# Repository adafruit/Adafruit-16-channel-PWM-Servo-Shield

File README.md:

# PCB for the Adafruit 16-channel PWM/Servo shield

__Format is EagleCAD schematic and board layout__

<a href="http://www.adafruit.com/products/1411"><br/>Click here to purchase one from the Adafruit shop</a>

You want to make a cool Arduino robot, maybe a hexapod walker, or maybe just a piece of art with a lot of moving parts. Or maybe you want to drive a lot of LEDs with precise PWM output. Then you realize that the Arduino has only a few PWM outputs, and maybe those outputs are conflicting with another shield! What now? You could give up OR you could just get our handy PWM and Servo driver shield. It's just like our popular PWM/Servo Breakout but now Arduino-ready and works with any Arduino that uses shields: Uno, Leo, Mega, ADK, its all good.

When we saw this chip, we quickly realized what an excellent add-on this would be. __Using only two I2C pins, control 16 free-running PWM outputs!__ You can even stack up 62 shields to control up to 992 PWM outputs (which we would really like to see since it would be glorious and like 4 feet tall) Because I2C is a shared bus you can also connect other I2C devices and sensors to the SCL/SDA pins as long as their addresses don't conflict (this shield has address 0x40)

- There's an I2C-controlled PWM driver with a built in clock. That means that, unlike the TLC5940 family, you do not need to continuously send it signal tying up your microcontroller, its completely free running!
- It is 5V compliant, which means you can control it from a 3.3V Arduino and still safely drive up to 6V outputs (this is good for when you want to control white or blue LEDs with 3.4+ forward voltages)
- 6 address select pins so you can stack up to 62 of these on a single i2c bus. 12 out of 16 output pins can be accessed when stacked.
- Adjustable frequency PWM up to about 1.6 KHz
- 12-bit resolution for each output - for servos, that means about 4us resolution at 60Hz update rate
- Configurable push-pull or open-drain output

We wrapped up this lovely chip into a shield with a couple nice extras

- Terminal block for power input (or you can use the 0.1" breakouts on the side)
- Reverse polarity protection on the terminal block input
- Green and red power-good LEDs
- 3 pin connectors in groups of 4 so you can plug in 16 servos at once (Servo plugs are slightly wider than 0.1" so you can only stack 4 next to each other on 0.1" header
- Stackable design. You'll need to pick up stacking headers and right angle 3x4 headers in order to stack on top of this shield without the servo connections getting in the way.
- A spot to place a big capacitor on the V+ line (in case you need it)
- 220 ohm series resistors on all the output lines to protect them, and to make driving LEDs trivial
- Solder jumpers for the 6 address select pins
- A lot of extra space remaining? Let's turn it into a prototyping area. You get a 5x20 proto area for any extra wiring you'd like to add

This product comes with a fully tested and assembled shield as well as 4 pieces of 3x4 male straight header (for servo/LED plugs), a 2-pin terminal block (for power) and a stick of 0.1" header so you can plug into an Arduino. A little light soldering will be required to assemble and customize the board by attaching the desired headers but it is a 15 minute task that even a beginner can do. [If you want to use right-angle 3x4 headers, we also carry a 4 pack in the shop - note that only 3 of them can be used when stacking (12 servos total)](http://www.adafruit.com/products/816).

__Servos and Arduino not included__ - but we do sell tons of different servos in the shop so pick up a few while you're here!

## License

Adafruit invests time and resources providing this open source design, 
please support Adafruit and open-source hardware by purchasing 
products from Adafruit!

Designed by Adafruit Industries.  
Creative Commons Attribution, Share-Alike license, check license.txt for more information
All text above must be included in any redistribution

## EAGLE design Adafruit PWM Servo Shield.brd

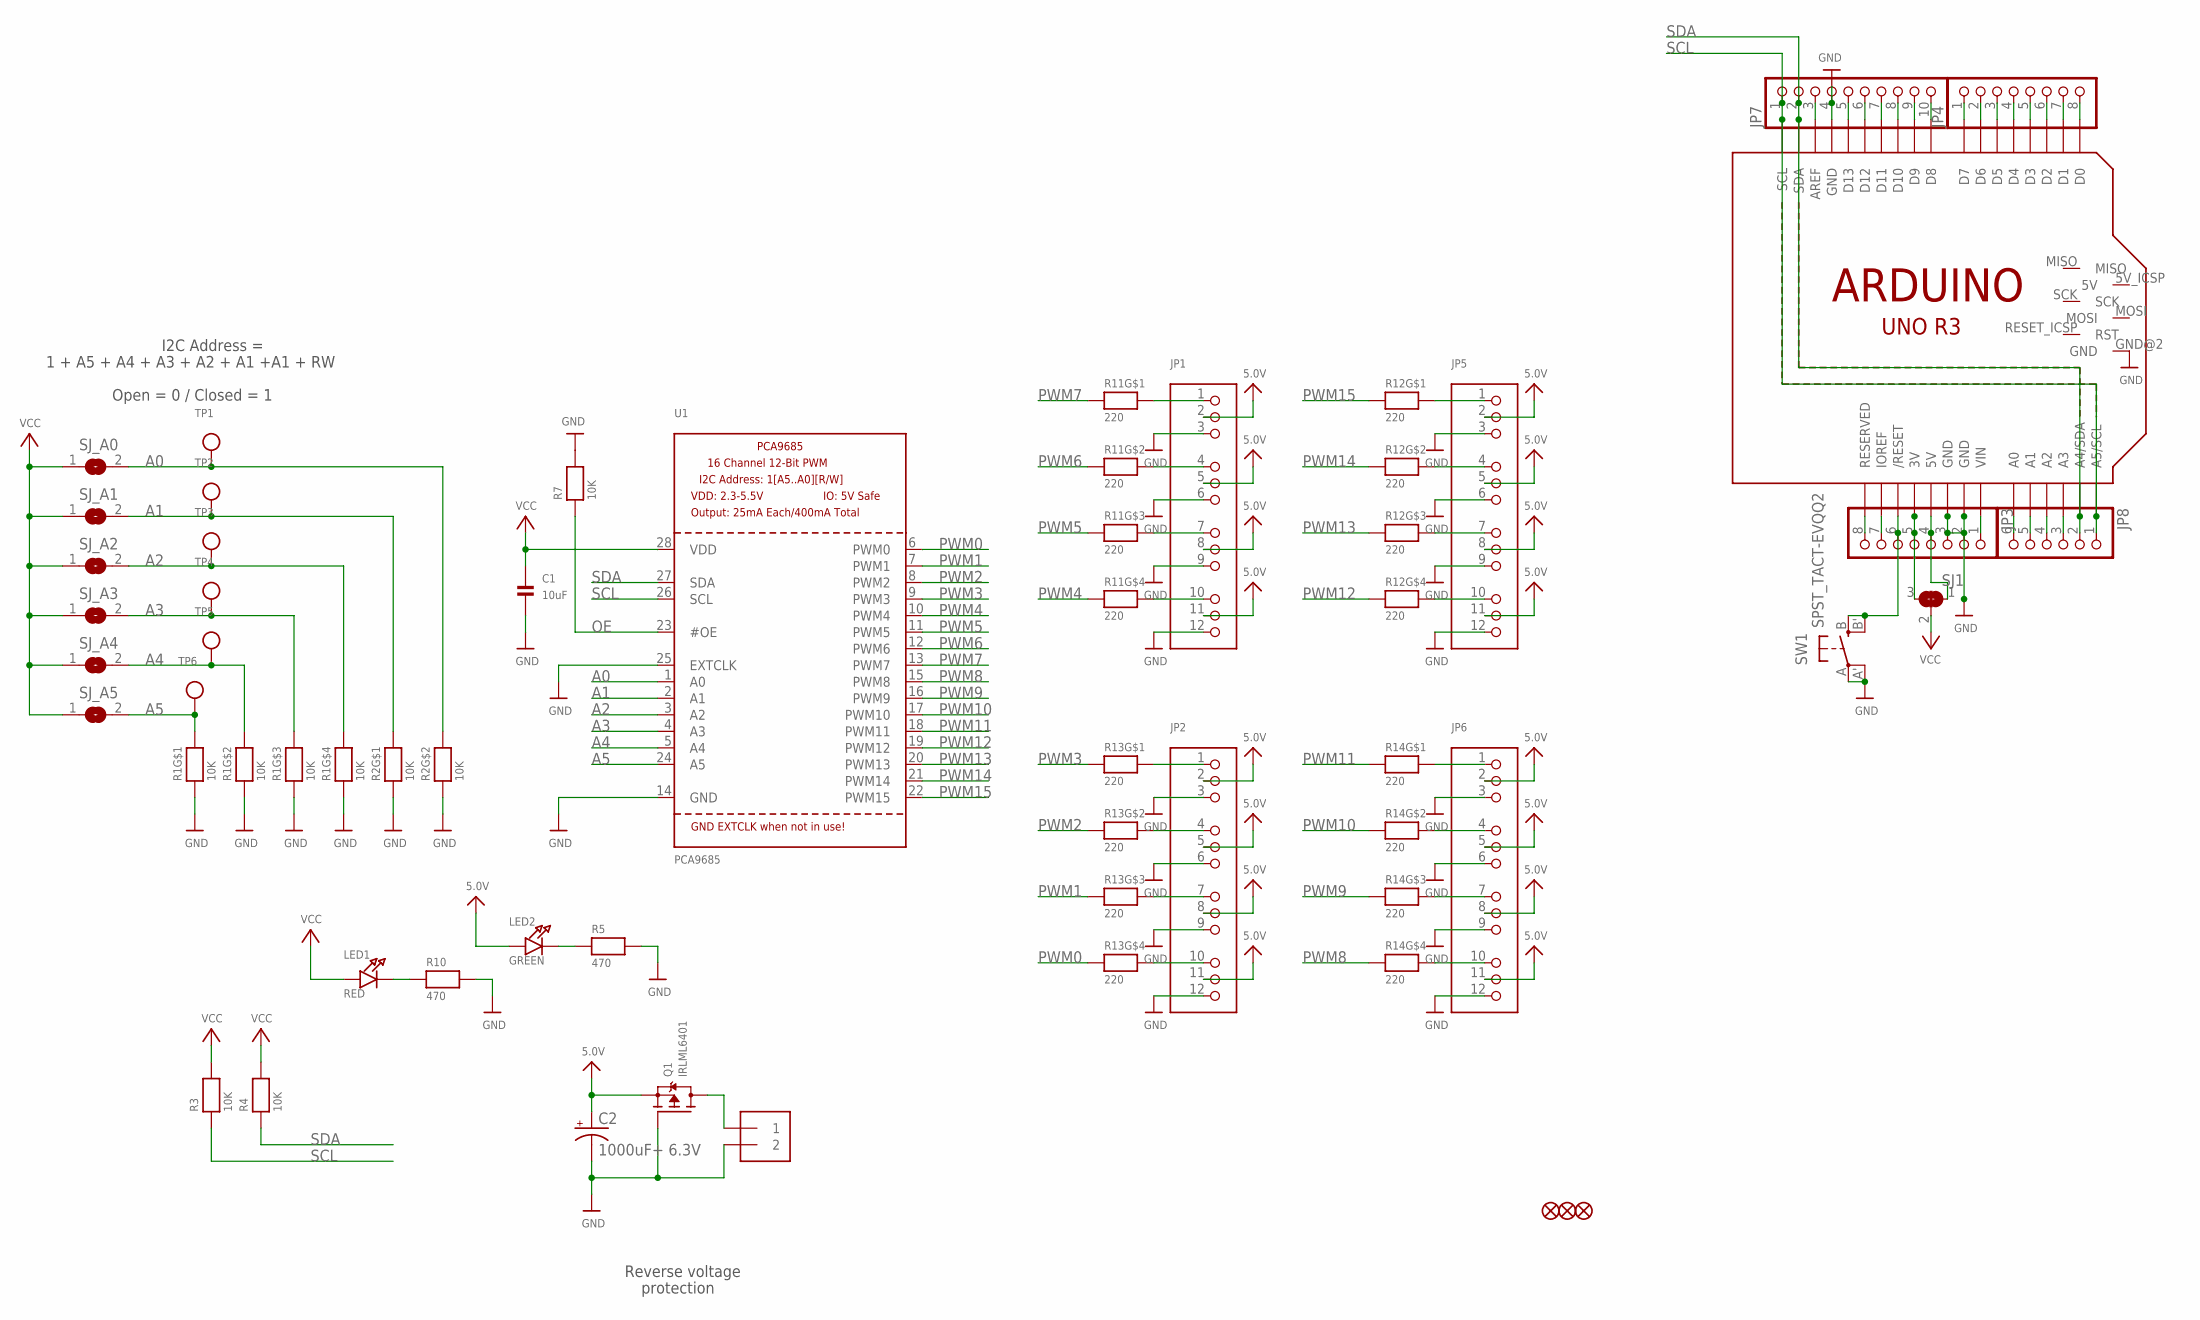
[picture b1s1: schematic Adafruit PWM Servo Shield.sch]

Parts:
C1: 10uF; 0805
C2: 1000uF+ 6.3V; E3,5-10
FID1, FID2, FID3: FIDUCIAL""; FIDUCIAL_1MM
J1: TERMBLOCK_1X2-3.5MM; 1X2-3.5MM
JP1, JP2, JP5, JP6: HEADER-3X04; 3X04
JP3, JP4: PINHD-1X8CLEANBIG; 1X08-CLEANBIG
JP7: HEADER-1X1070MIL; 1X10_ROUND70
JP8: PINHD-1X6CB; 1X06-CLEANBIG
LED1: RED; CHIPLED_0805
LED2: GREEN; CHIPLED_0805
Q1: IRLML6401; SOT23-WIDE
R1, R2: 10K; RESPACK_4X0603
R3, R4, R7: 10K; 0805
R5, R10: 470; 0805
R11, R12, R13, R14: 220; RESPACK_4X0603
SJ1: SOLDERJUMPER_2WAY; SOLDERJUMPER_2WAY_OPEN_NOPASTE
SJ_A0, SJ_A1, SJ_A2, SJ_A3, SJ_A4, SJ_A5: SOLDERJUMPERREFLOW_NOPASTE; SOLDERJUMPER_REFLOW_NOPASTE
SW1: SPST_TACT-EVQQ2; EVQ-Q2
TP1, TP2, TP3, TP4, TP5, TP6: TESTPOINTROUND2MM; TESTPOINT_ROUND_2MM
U1: PCA9685; TSSOP28
U$44: ARDUINO_R3_ICSP; ARDUINOR3_ICSP

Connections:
5.0V: C2.+, JP1.2, JP1.5, JP1.8, JP1.11, JP2.2, JP2.5, JP2.8, JP2.11, JP5.2, JP5.5, JP5.8, JP5.11, JP6.2, JP6.5, JP6.8, JP6.11, LED2.A, Q1.2 (S)
A0: R2.7 (2), SJ_A0.2, TP1.P$1, U1.1 (A0)
A1: R2.8 (2), SJ_A1.2, TP2.P$1, U1.2 (A1)
A2: R1.5 (2), SJ_A2.2, TP3.P$1, U1.3 (A2)
A3: R1.6 (2), SJ_A3.2, TP4.P$1, U1.4 (A3)
A4: R1.7 (2), SJ_A4.2, TP5.P$1, U1.5 (A4)
A5: R1.8 (2), SJ_A5.2, TP6.P$1, U1.24 (A5)
GND: C1.2, C2.-, J1.2, JP1.3, JP1.6, JP1.9, JP1.12, JP2.3, JP2.6, JP2.9, JP2.12, JP3.2, JP3.3, JP5.3, JP5.6, JP5.9, JP5.12, JP6.3, JP6.6, JP6.9, JP6.12, JP7.4, Q1.1 (G), R1.1, R1.2 (1), R1.3 (1), R1.4 (1), R2.1, R2.2 (1), R5.2, R7.2, R10.2, SW1.A, SW1.A' (P1), U1.14 (GND), U1.25 (EXTCLK), U$44.GND, U$44.GND@1 (GND), U$44.GND@2 (GND), U$44.GND@3 (GND)
unnamed: LED1.C, R10.1
unnamed: JP1.4, R11.7 (2)
unnamed: JP1.1, R11.8 (2)
unnamed: JP1.7, R11.6 (2)
unnamed: JP1.10, R11.5 (2)
unnamed: JP2.1, R13.8 (2)
unnamed: JP2.4, R13.7 (2)
unnamed: JP2.7, R13.6 (2)
unnamed: JP2.10, R13.5 (2)
unnamed: JP6.10, R14.5 (2)
unnamed: JP6.7, R14.6 (2)
unnamed: JP6.4, R14.7 (2)
unnamed: JP6.1, R14.8 (2)
unnamed: JP5.10, R12.5 (2)
unnamed: JP5.7, R12.6 (2)
unnamed: JP5.4, R12.7 (2)
unnamed: JP5.1, R12.8 (2)
unnamed: JP3.1, U$44.VIN
unnamed: LED2.C, R5.1
unnamed: JP3.5, SJ1.3, U$44.3V
unnamed: JP3.4, SJ1.1, U$44.5V
unnamed: JP3.7, U$44.IOREF
unnamed: JP3.8, U$44.RESERVED
unnamed: JP4.1, U$44.D7
unnamed: JP4.2, U$44.D6
unnamed: JP4.3, U$44.D5
unnamed: JP4.4, U$44.D4
unnamed: JP4.5, U$44.D3
unnamed: JP4.6, U$44.D2
unnamed: JP4.7, U$44.D1
unnamed: JP4.8, U$44.D0
unnamed: JP7.3, U$44.AREF
unnamed: JP7.5, U$44.D13
unnamed: JP7.6, U$44.D12
unnamed: JP7.7, U$44.D11
unnamed: JP7.8, U$44.D10
unnamed: JP7.9, U$44.D9
unnamed: JP7.10, U$44.D8
unnamed: JP8.3, U$44.A3
unnamed: JP8.4, U$44.A2
unnamed: JP8.5, U$44.A1
unnamed: JP8.6, U$44.A0
unnamed: JP3.6, SW1.B (S), SW1.B' (S1), U$44.RESET (/RESET)
OE: R7.1, U1.23 (#OE)
PWM0: R13.4 (1), U1.6 (PWM0)
PWM1: R13.3 (1), U1.7 (PWM1)
PWM2: R13.2 (1), U1.8 (PWM2)
PWM3: R13.1, U1.9 (PWM3)
PWM4: R11.4 (1), U1.10 (PWM4)
PWM5: R11.3 (1), U1.11 (PWM5)
PWM6: R11.2 (1), U1.12 (PWM6)
PWM7: R11.1, U1.13 (PWM7)
PWM8: R14.4 (1), U1.15 (PWM8)
PWM9: R14.3 (1), U1.16 (PWM9)
PWM10: R14.2 (1), U1.17 (PWM10)
PWM11: R14.1, U1.18 (PWM11)
PWM12: R12.4 (1), U1.19 (PWM12)
PWM13: R12.3 (1), U1.20 (PWM13)
PWM14: R12.2 (1), U1.21 (PWM14)
PWM15: R12.1, U1.22 (PWM15)
PWRIN: J1.1, Q1.3 (D)
SCL: JP7.1, JP8.1, R3.1, U1.26 (SCL), U$44.A5 (A5/SCL), U$44.SCL
SDA: JP7.2, JP8.2, R4.1, U1.27 (SDA), U$44.A4 (A4/SDA), U$44.SDA
VCC: C1.1, LED1.A, R3.2, R4.2, SJ1.2, SJ_A0.1, SJ_A1.1, SJ_A2.1, SJ_A3.1, SJ_A4.1, SJ_A5.1, U1.28 (VDD)

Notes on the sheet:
Reverse voltage
protection
1 + A5 + A4 + A3 + A2 + A1 +A1 + RW
I2C Address =
Open = 0 / Closed = 1

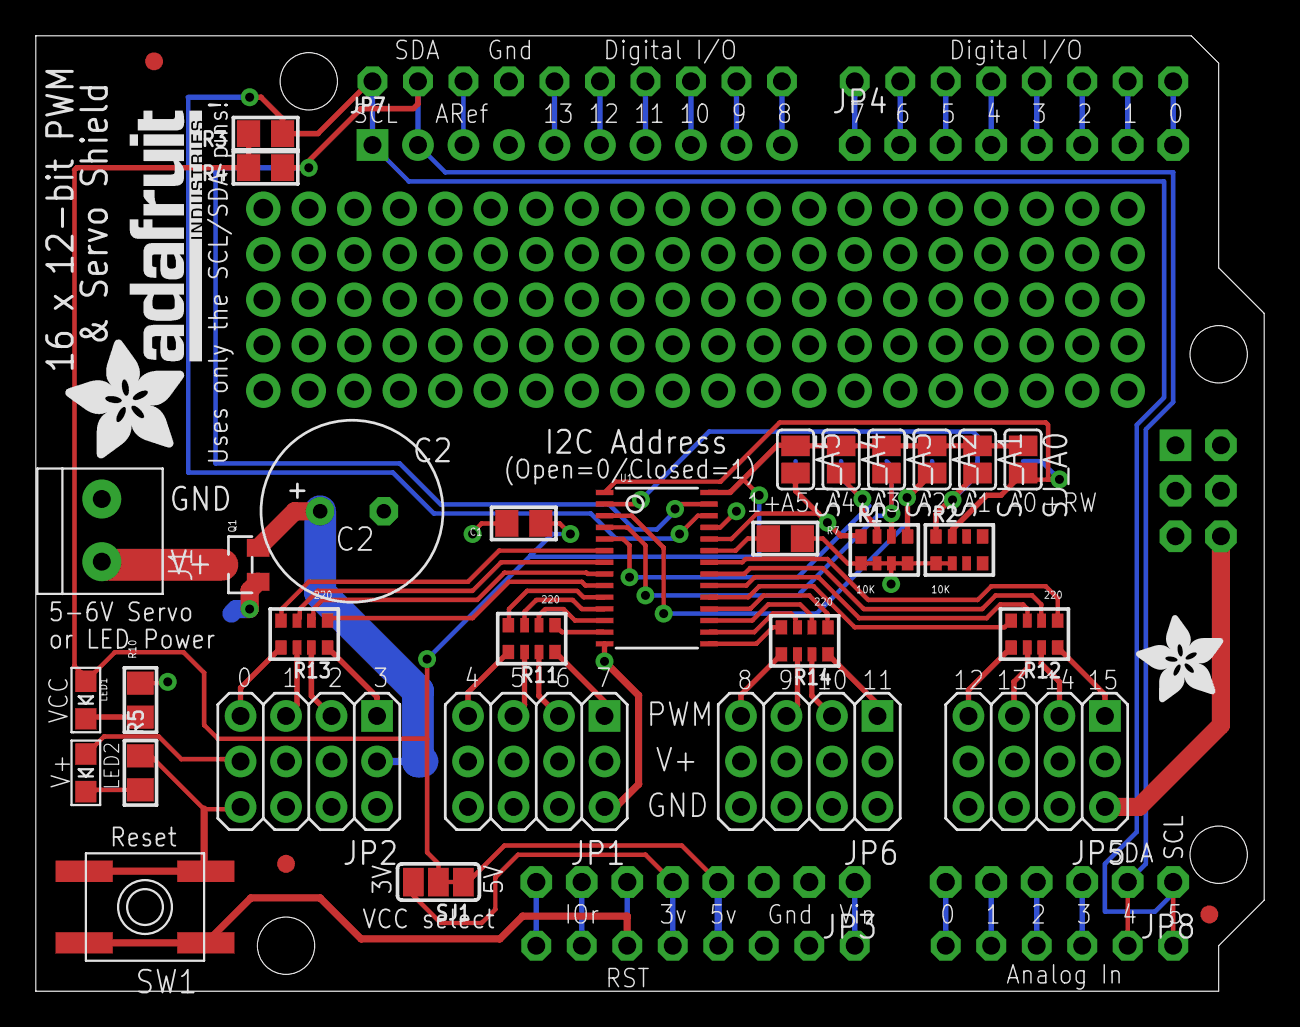
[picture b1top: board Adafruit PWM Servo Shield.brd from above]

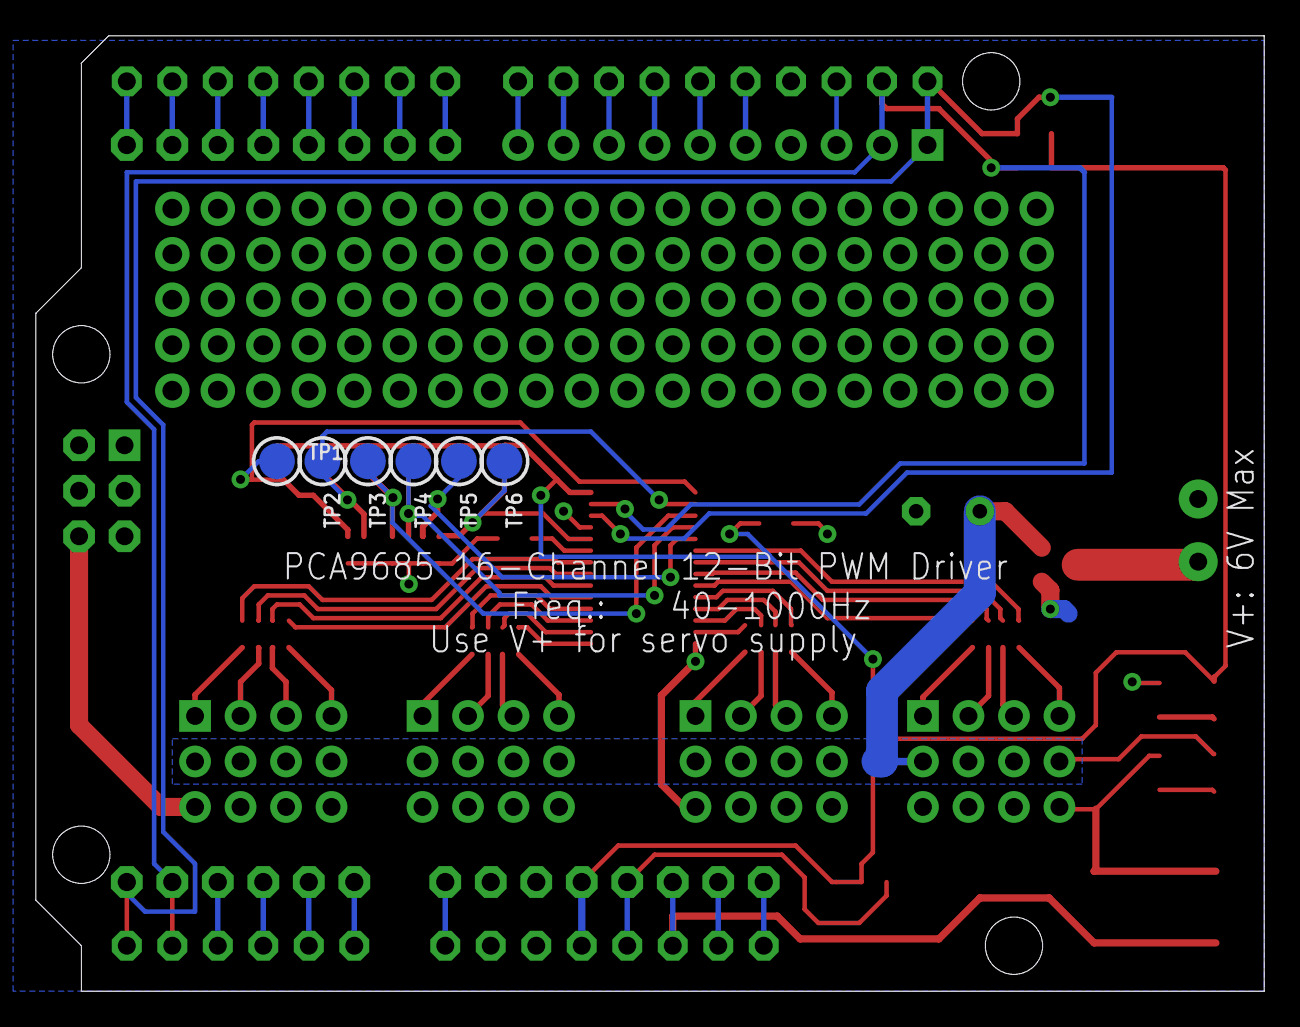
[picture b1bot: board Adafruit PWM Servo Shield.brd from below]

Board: 2 copper layers, 68.6 x 53.3 mm, 46 parts (6 on the bottom side), 72 nets.

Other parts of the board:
U$51: ADAFRUIT_5MM
U$54: ADAFRUIT_TEXT_20MM

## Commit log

2013-12-18 init
2019-05-08 readme + image
